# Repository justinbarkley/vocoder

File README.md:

# vocoder-clean
a cleanup for my previous repository on the vocoder

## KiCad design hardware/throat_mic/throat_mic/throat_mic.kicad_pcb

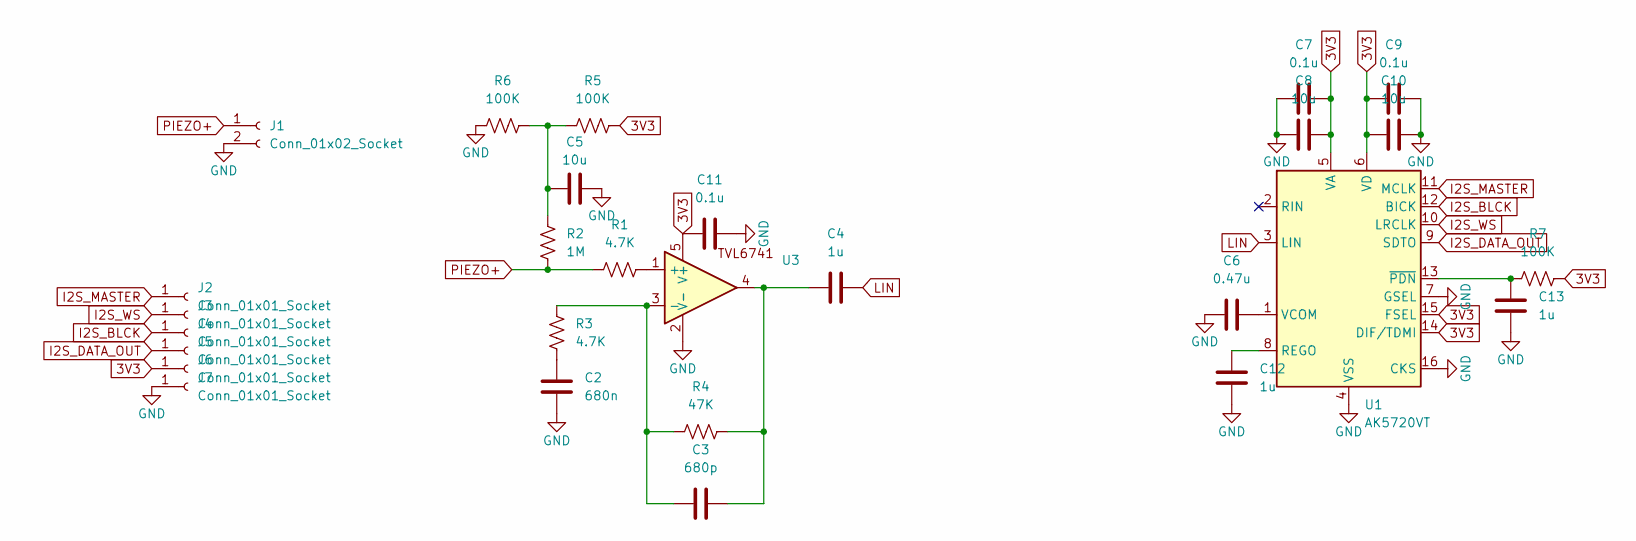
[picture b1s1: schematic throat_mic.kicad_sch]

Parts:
C2: 680n; C_0603_1608Metric
C3: 680p; C_0603_1608Metric
C4, C12, C13: 1u; C_0603_1608Metric
C5, C8, C10: 10u; C_0603_1608Metric
C6: 0.47u; C_0603_1608Metric
C7, C9, C11: 0.1u; C_0603_1608Metric
J1: Conn_01x02_Socket; PinHeader_1x02_P2.54mm_Vertical
J2, J3, J4, J5, J6, J7: Conn_01x01_Socket; PinHeader_1x01_P1.00mm_Vertical
R1, R3: 4.7K; R_0603_1608Metric
R2: 1M; R_0603_1608Metric
R4: 47K; R_0603_1608Metric
R5, R6, R7: 100K; R_0603_1608Metric
U1: AK5720VT; TSSOP-16_4.4x5mm_P0.65mm
U3: SOT-353_SC-70-5

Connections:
3V3: C7.1, C8.1, C9.2, C10.2, C11.1, J6.1 (Pin_1_1), R5.2, R7.2, U1.5 (VA), U1.6 (VD), U1.14 (DIF/TDMI), U1.15 (FSEL), U3.5 (V+)
GND: C2.1, C5.2, C6.2, C7.2, C8.2, C9.1, C10.1, C11.2, C12.2, C13.2, J1.2, J7.1 (Pin_1_1), R6.1, U1.4 (VSS), U1.7 (GSEL), U1.16 (CKS), U3.2 (V-)
I2S_BLCK: J4.1 (Pin_1_1), U1.12 (BICK)
I2S_DATA_OUT: J5.1 (Pin_1_1), U1.9 (SDTO)
I2S_MASTER: J2.1 (Pin_1_1), U1.11 (MCLK)
I2S_WS: J3.1 (Pin_1_1), U1.10 (LRCLK)
LIN: C4.1, U1.3 (LIN)
unnamed: C2.2, R3.2
unnamed: C3.1, C4.2, R4.2, U3.4
unnamed: C5.1, R2.1, R5.1, R6.2
unnamed: C12.1, U1.8 (REGO)
unnamed: C6.1, U1.1 (VCOM)
unnamed: C13.1, R7.1, U1.13 (~PDN)
unnamed: R1.1, U3.1 (+)
unnamed: C3.2, R3.1, R4.1, U3.3 (-)
PIEZO+: J1.1, R1.2, R2.2

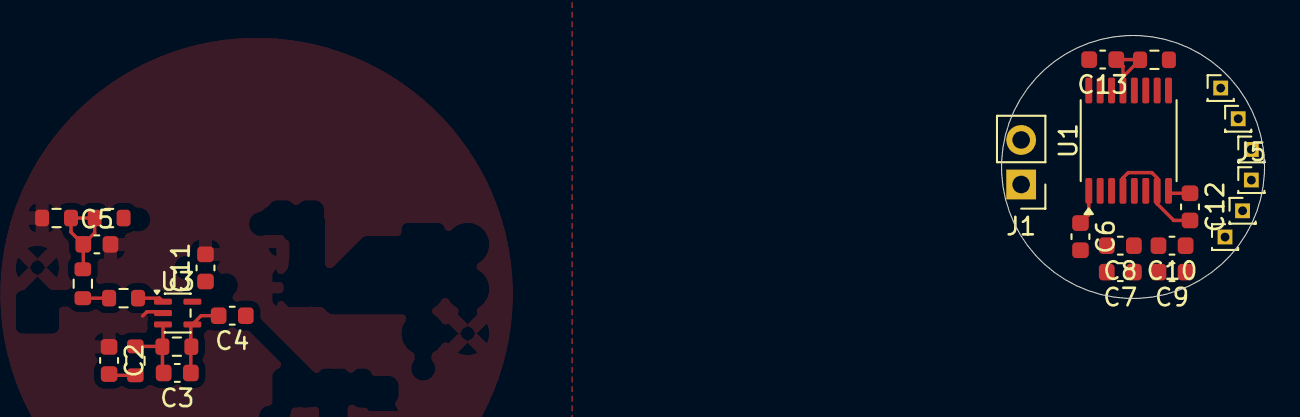
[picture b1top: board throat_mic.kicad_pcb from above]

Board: 2 copper layers, 15.0 x 15.0 mm, 28 parts (0 on the bottom side), 16 nets.

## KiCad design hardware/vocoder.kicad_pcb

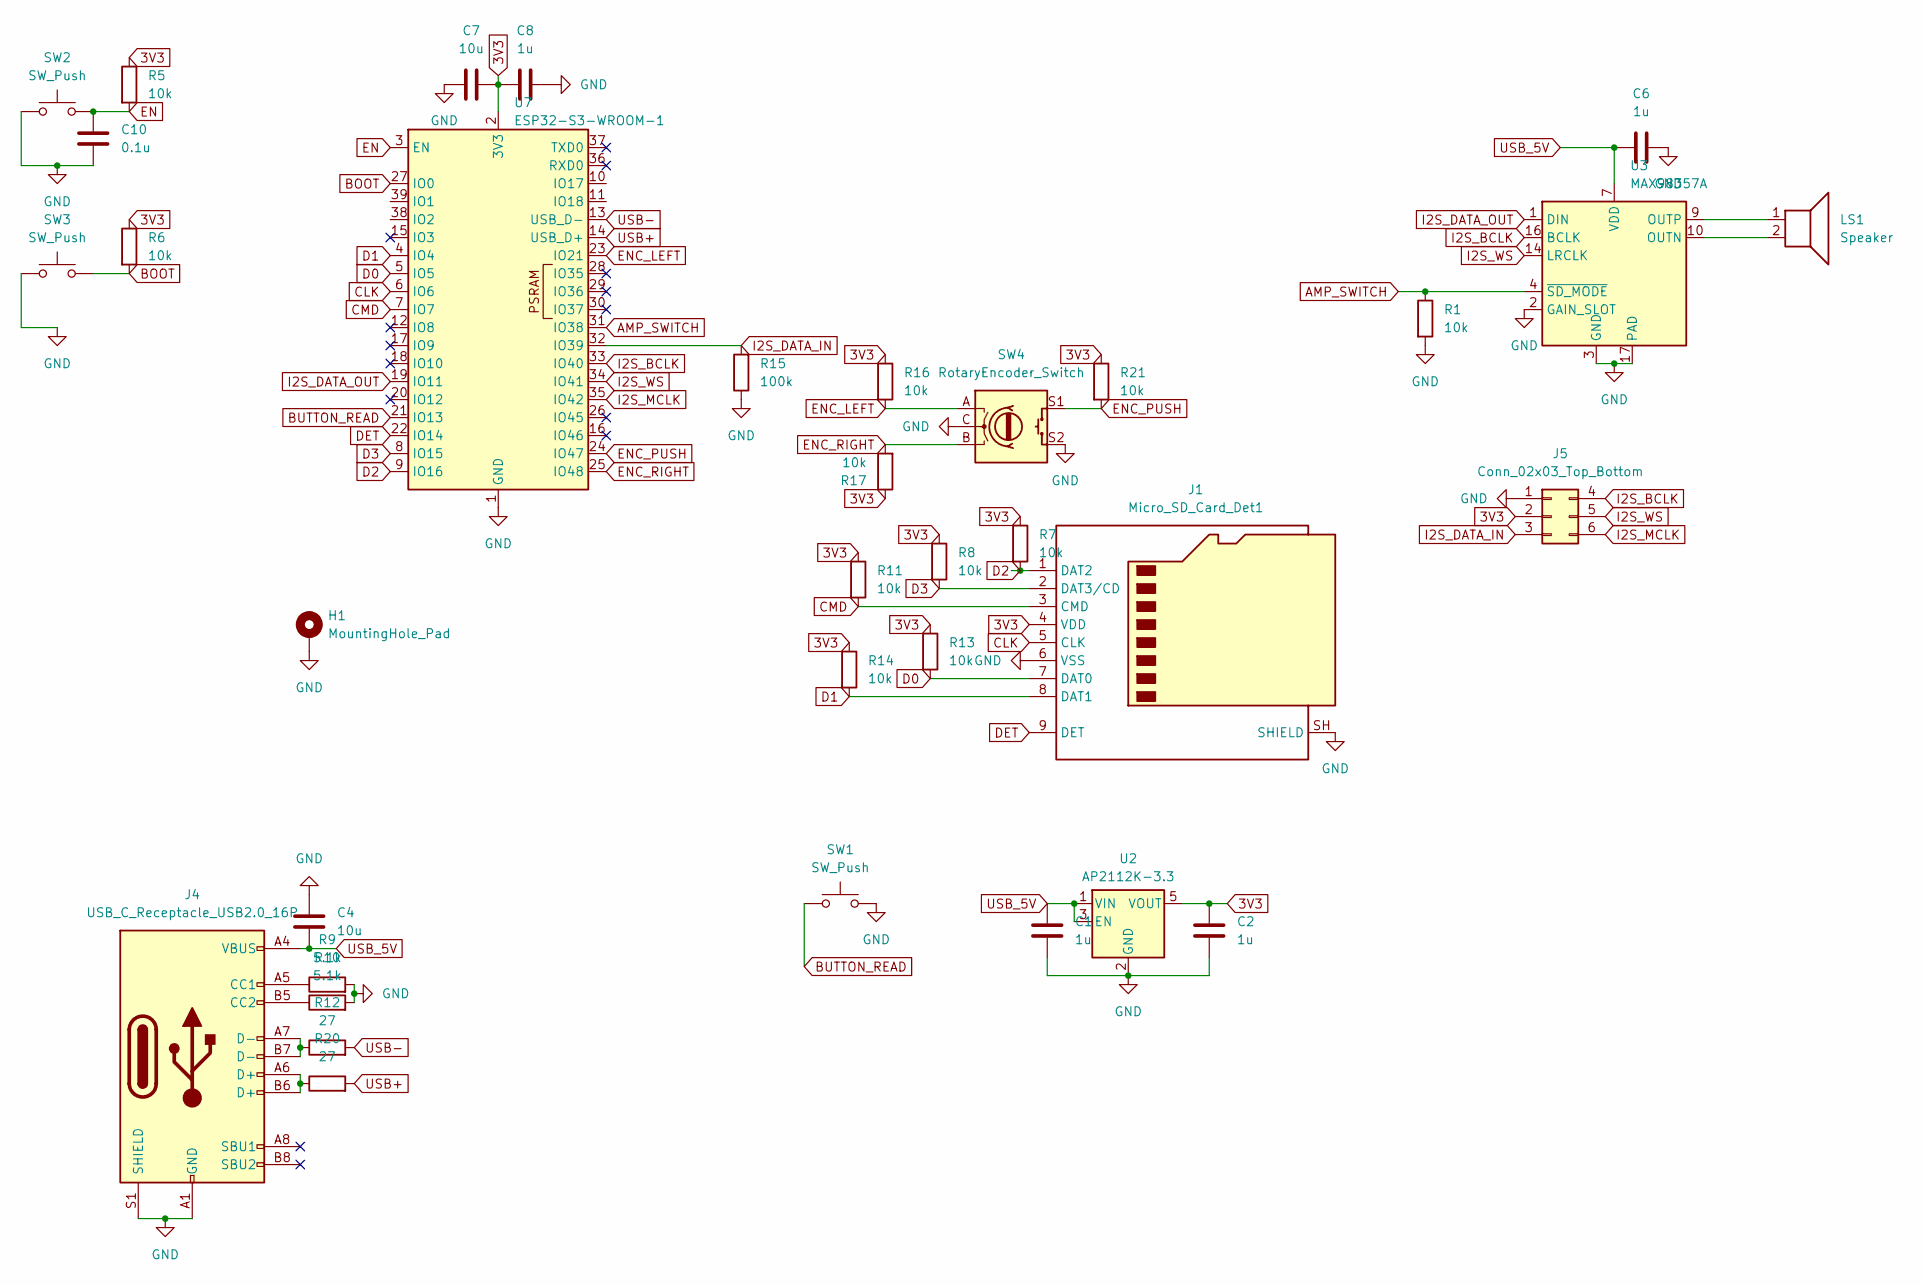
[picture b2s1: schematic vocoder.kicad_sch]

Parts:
C1, C2, C6, C8: 1u; C_0603_1608Metric
C4, C7: 10u; C_0805_2012Metric
C10: 0.1u; C_0603_1608Metric
H1: MountingHole_Pad; MountingHole_3.2mm_M3_DIN965_Pad
J1: Micro_SD_Card_Det1; Untitled
J4: USB_C_Receptacle_USB2.0_16P; USB_C_Receptacle_GCT_USB4105-xx-A_16P_TopMnt_Horizontal
J5: Conn_02x03_Top_Bottom; PinHeader_1x06_P2.54mm_Vertical
LS1: Speaker; TerminalBlock_MaiXu_MX126-5.0-02P_1x02_P5.00mm
R1, R5, R6, R7, R8, R11, R13, R14, R16, R17, R21: 10k; R_0603_1608Metric_Pad0.98x0.95mm_HandSolder
R9, R10: 5.1k; R_0603_1608Metric_Pad0.98x0.95mm_HandSolder
R12, R20: 27; R_0603_1608Metric_Pad0.98x0.95mm_HandSolder
R15: 100k; R_0603_1608Metric_Pad0.98x0.95mm_HandSolder
SW1: SW_Push; SW_Tactile_SPST_Angled_PTS645Vx58-2LFS
SW2, SW3: SW_Push; SW_SPST_TS-1088-xR020
SW4: RotaryEncoder_Switch; RotaryEncoder_Bourns_Horizontal_PEC12R-2x17F-Sxxxx
U2: AP2112K-3.3; SOT-23-5
U3: MAX98357A; TQFN-16-1EP_3x3mm_P0.5mm_EP1.23x1.23mm
U7: ESP32-S3-WROOM-1; ESP32-S3-WROOM-1U

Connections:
3V3: C2.1, C7.2, C8.1, J1.4 (VDD), J5.2, R5.1, R6.1, R7.1, R8.1, R11.1, R13.1, R14.1, R16.1, R17.1, R21.1, U2.5 (VOUT), U7.2 (3V3)
AMP_SWITCH: R1.1, U3.4 (~SD_MODE), U7.31 (IO38)
BOOT: R6.2, SW3.2, U7.27 (IO0)
BUTTON_READ: SW1.1, U7.21 (IO13)
CLK: J1.5 (CLK), U7.6 (IO6)
CMD: J1.3 (CMD), R11.2, U7.7 (IO7)
D0: J1.7 (DAT0), R13.2, U7.5 (IO5)
D1: J1.8 (DAT1), R14.2, U7.4 (IO4)
D2: J1.1 (DAT2), R7.2, U7.9 (IO16)
D3: J1.2 (DAT3/CD), R8.2, U7.8 (IO15)
DET: J1.9 (DET), U7.22 (IO14)
EN: C10.1, R5.2, SW2.2, U7.3 (EN)
ENC_LEFT: R16.2, SW4.A, U7.23 (IO21)
ENC_PUSH: R21.2, SW4.S1, U7.24 (IO47)
ENC_RIGHT: R17.2, SW4.B, U7.25 (IO48)
GND: C1.2, C2.2, C4.2, C6.2, C7.1, C8.2, C10.2, H1.1 (1_1), J1.6 (VSS), J1.SH (SHIELD), J4.A1 (GND), J4.A12 (GND), J4.B1 (GND), J4.B12 (GND), J4.S1 (SHIELD), J5.1, R1.2, R9.2, R10.2, R15.1, SW1.2, SW2.1, SW3.1, SW4.C, SW4.S2, U2.2 (GND), U3.2 (GAIN_SLOT), U3.3 (GND), U3.11 (GND), U3.15 (GND), U3.17 (PAD), U7.1 (GND), U7.40 (GND), U7.41 (GND)
I2S_BCLK: J5.4, U3.16 (BCLK), U7.33 (IO40)
I2S_DATA_IN: J5.3, R15.2, U7.32 (IO39)
I2S_DATA_OUT: U3.1 (DIN), U7.19 (IO11)
I2S_MCLK: J5.6, U7.35 (IO42)
I2S_WS: J5.5, U3.14 (LRCLK), U7.34 (IO41)
unnamed: J4.A5 (CC1), R9.1
unnamed: J4.B5 (CC2), R10.1
unnamed: J4.A6 (D+), J4.B6 (D+), R20.1
unnamed: J4.A7 (D-), J4.B7 (D-), R12.1
unnamed: LS1.2, U3.10 (OUTN)
unnamed: LS1.1, U3.9 (OUTP)
USB+: R20.2, U7.14 (USB_D+)
USB-: R12.2, U7.13 (USB_D-)
USB_5V: C1.1, C4.1, C6.1, J4.A4 (VBUS), J4.A9 (VBUS), J4.B4 (VBUS), J4.B9 (VBUS), U2.1 (VIN), U2.3 (EN), U3.7 (VDD), U3.8 (VDD)

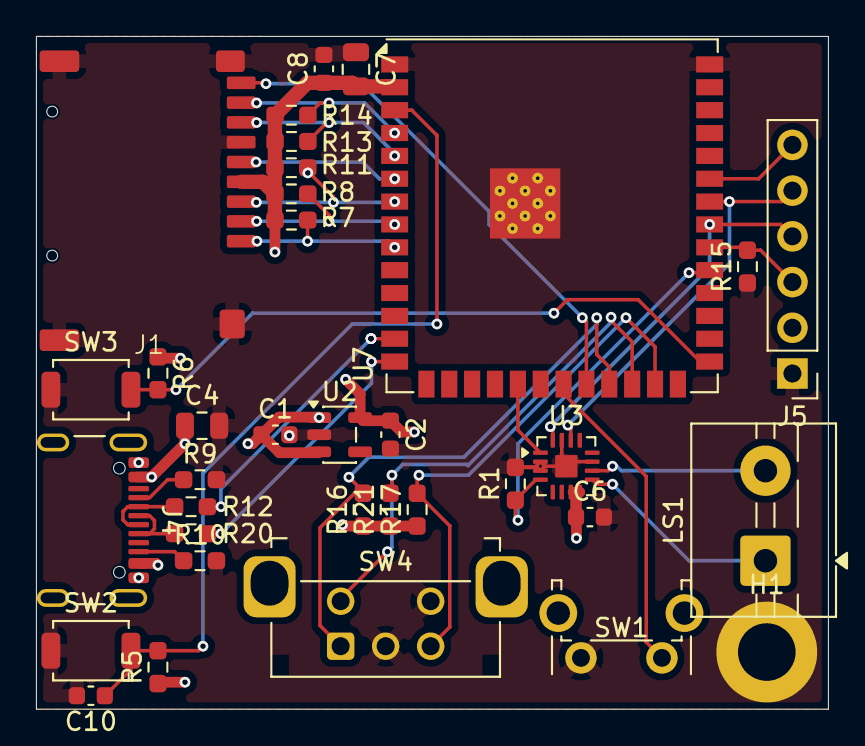
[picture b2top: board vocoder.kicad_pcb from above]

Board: 4 copper layers, 44.0 x 37.4 mm, 35 parts (0 on the bottom side), 30 nets.

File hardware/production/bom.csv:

Designator,Footprint,Quantity,Value,LCSC Part #
"C1, C2, C6, C8",0603,4,1u,
C10,0603,1,0.1u,
"C4, C7",0805,2,10u,
J1,Untitled,1,Micro_SD_Card_Det1,
J4,USB_C_Receptacle_GCT_USB4105-xx-A_16P_TopMnt_Horizontal,1,USB_C_Receptacle_USB2.0_16P,
J5,PinHeader_1x06_P2.54mm_Vertical,1,Conn_02x03_Top_Bottom,
LS1,TerminalBlock_MaiXu_MX126-5.0-02P_1x02_P5.00mm,1,Speaker,
"R1, R11, R13, R14, R16, R17, R21, R5, R6, R7, R8",0603,11,10k,
"R10, R9",0603,2,5.1k,
"R12, R20",0603,2,27,
R15,0603,1,100k,
SW1,SW_Tactile_SPST_Angled_PTS645Vx58-2LFS,1,SW_Push,
"SW2, SW3",SW_SPST_TS-1088-xR020,2,SW_Push,
SW4,RotaryEncoder_Bourns_Horizontal_PEC12R-2x17F-Sxxxx,1,RotaryEncoder_Switch,
U2,SOT-23-5,1,AP2112K-3.3,
U3,TQFN-16-1EP_3x3mm_P0.5mm_EP1.23x1.23mm,1,MAX98357A,
U7,ESP32-S3-WROOM-1U,1,ESP32-S3-WROOM-1,
